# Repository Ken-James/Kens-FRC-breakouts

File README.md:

# Kens-FRC-breakouts
Low-cost breakout boards for the FIRST robotics competition

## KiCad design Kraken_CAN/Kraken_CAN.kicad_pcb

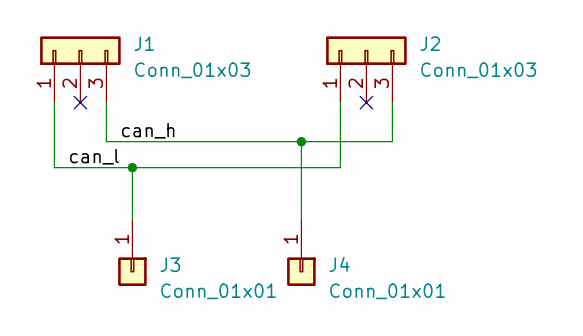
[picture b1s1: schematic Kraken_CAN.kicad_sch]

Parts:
J1, J2: Conn_01x03; PinSocket_1x03_P2.54mm_Vertical
J3, J4: Conn_01x01; MountingHole_2.7mm_M2.5_DIN965_Pad

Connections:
/can_h: J1.3, J2.3, J4.1
/can_l: J1.1, J2.1, J3.1

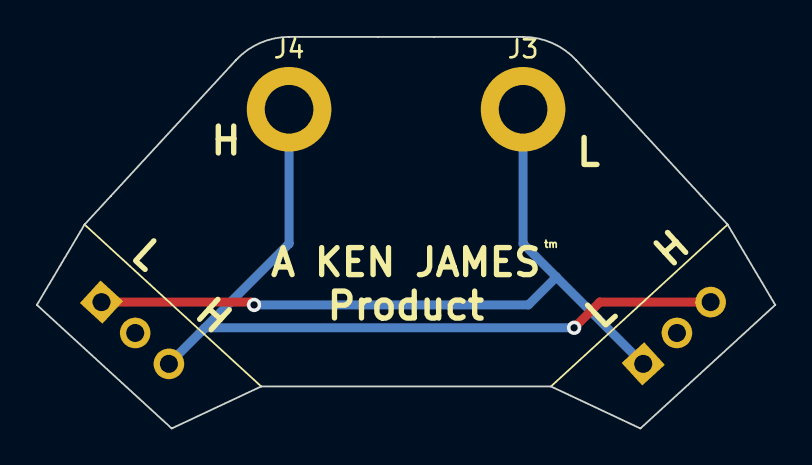
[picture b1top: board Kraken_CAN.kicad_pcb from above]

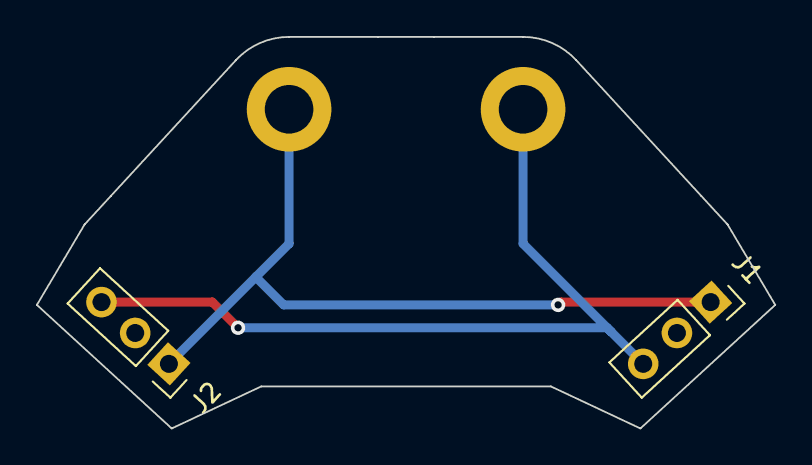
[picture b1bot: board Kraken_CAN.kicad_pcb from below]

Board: 2 copper layers, 41.0 x 21.8 mm, 4 parts (2 on the bottom side), 2 nets.

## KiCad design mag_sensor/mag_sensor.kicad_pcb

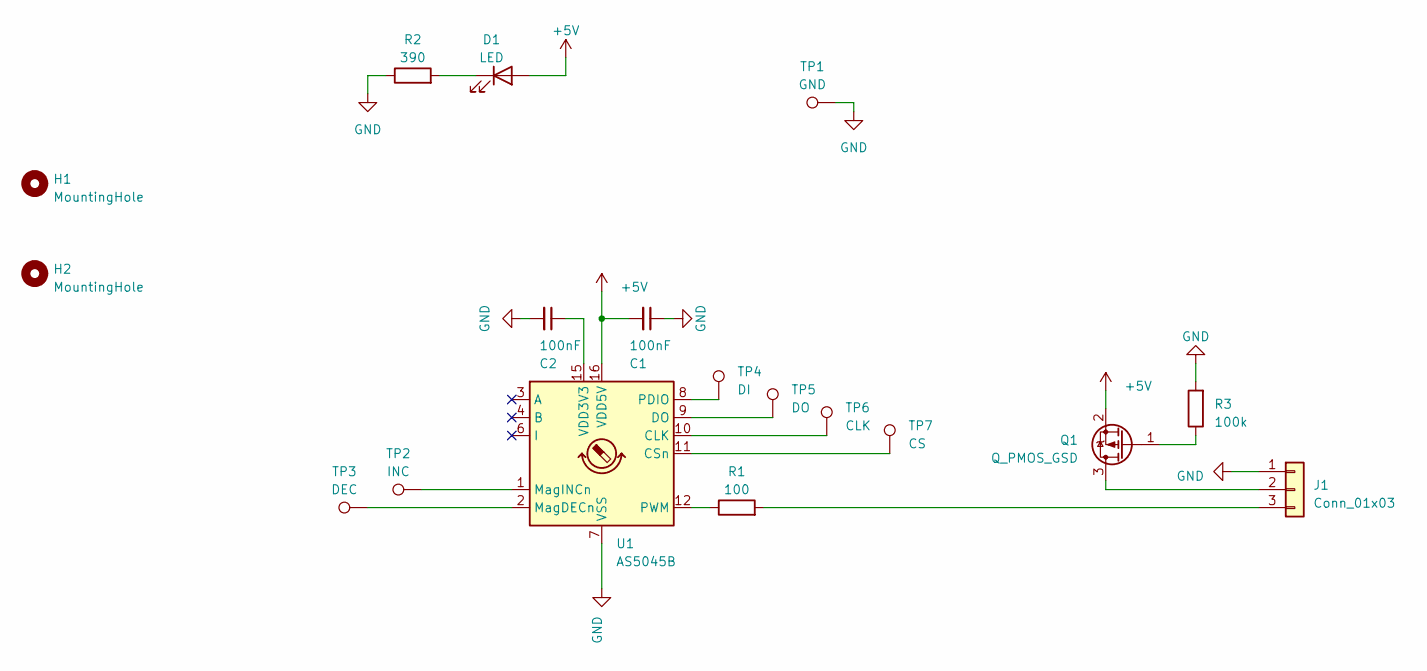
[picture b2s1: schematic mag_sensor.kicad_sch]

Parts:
C1, C2: 100nF; C_0603_1608Metric
D1: LED; LED_D3.0mm
H1, H2: MountingHole; MountingHole_2.7mm
J1: Conn_01x03; PinHeader_1x03_P2.54mm_Horizontal
Q1: Q_PMOS_GSD; SOT-23
R1: 100; R_0603_1608Metric
R2: 390; R_0603_1608Metric
R3: 100k; R_0603_1608Metric
TP1: GND; TestPoint_Pad_D1.0mm
TP2: INC; TestPoint_Pad_D1.0mm
TP3: DEC; TestPoint_Pad_D1.0mm
TP4: DI; TestPoint_Pad_D1.0mm
TP5: DO; TestPoint_Pad_D1.0mm
TP6: CLK; TestPoint_Pad_D1.0mm
TP7: CS; TestPoint_Pad_D1.0mm
U1: AS5045B; SSOP-16_5.3x6.2mm_P0.65mm

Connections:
+5V: C1.2, D1.2 (A), Q1.2 (S), U1.16 (VDD5V)
GND: C1.1, C2.2, J1.1, R2.1, R3.2, TP1.1, U1.7 (VSS)
unnamed: D1.1 (K), R2.2
unnamed: J1.2, Q1.3 (D)
unnamed: J1.3, R1.2
unnamed: Q1.1 (G), R3.1
unnamed: TP6.1, U1.10 (CLK)
unnamed: TP7.1, U1.11 (CSn)
unnamed: TP5.1, U1.9 (DO)
unnamed: TP3.1, U1.2 (MagDECn)
unnamed: TP2.1, U1.1 (MagINCn)
unnamed: TP4.1, U1.8 (PDIO)
unnamed: R1.1, U1.12 (PWM)
unnamed: C2.1, U1.15 (VDD3V3)

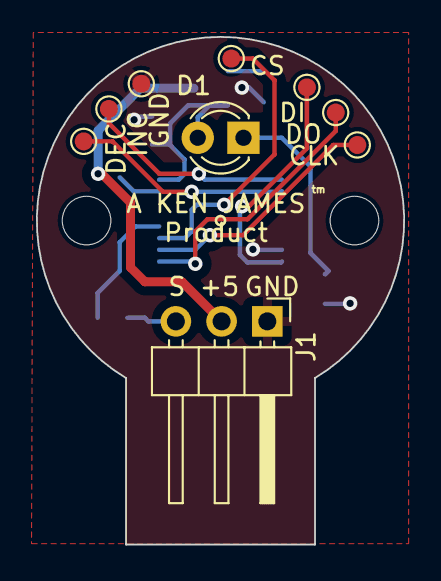
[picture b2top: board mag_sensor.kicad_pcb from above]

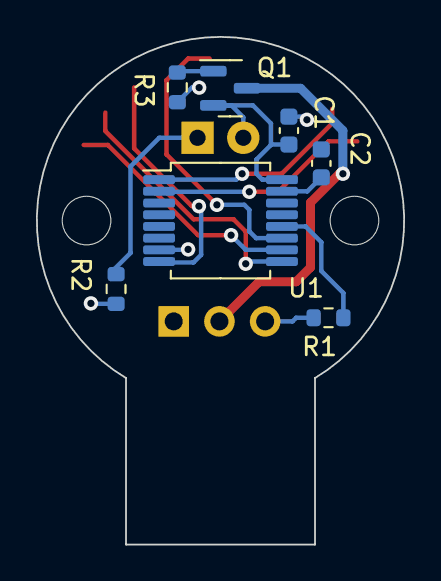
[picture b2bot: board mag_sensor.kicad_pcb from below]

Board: 2 copper layers, 20.4 x 28.2 mm, 18 parts (7 on the bottom side), 14 nets.
